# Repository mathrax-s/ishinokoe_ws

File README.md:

# いしのこえWS

いしのこえWSは、MATHRAXの作品「いしのこえ」を紹介・解説しながら、石に触れると音を奏でるちいさな「いしのこえ」をつくるワークショップです。
自分のピンとくる1つの石を選んだら、その相棒となる2つ目の石を選びます。
ここにあるプログラムは、タッチすると音を奏でるプログラムです。

Seeduino XIAOにプログラムします。
<hr />
<p align="center">
</img></img>
<hr />
</img>
<hr />
</p>

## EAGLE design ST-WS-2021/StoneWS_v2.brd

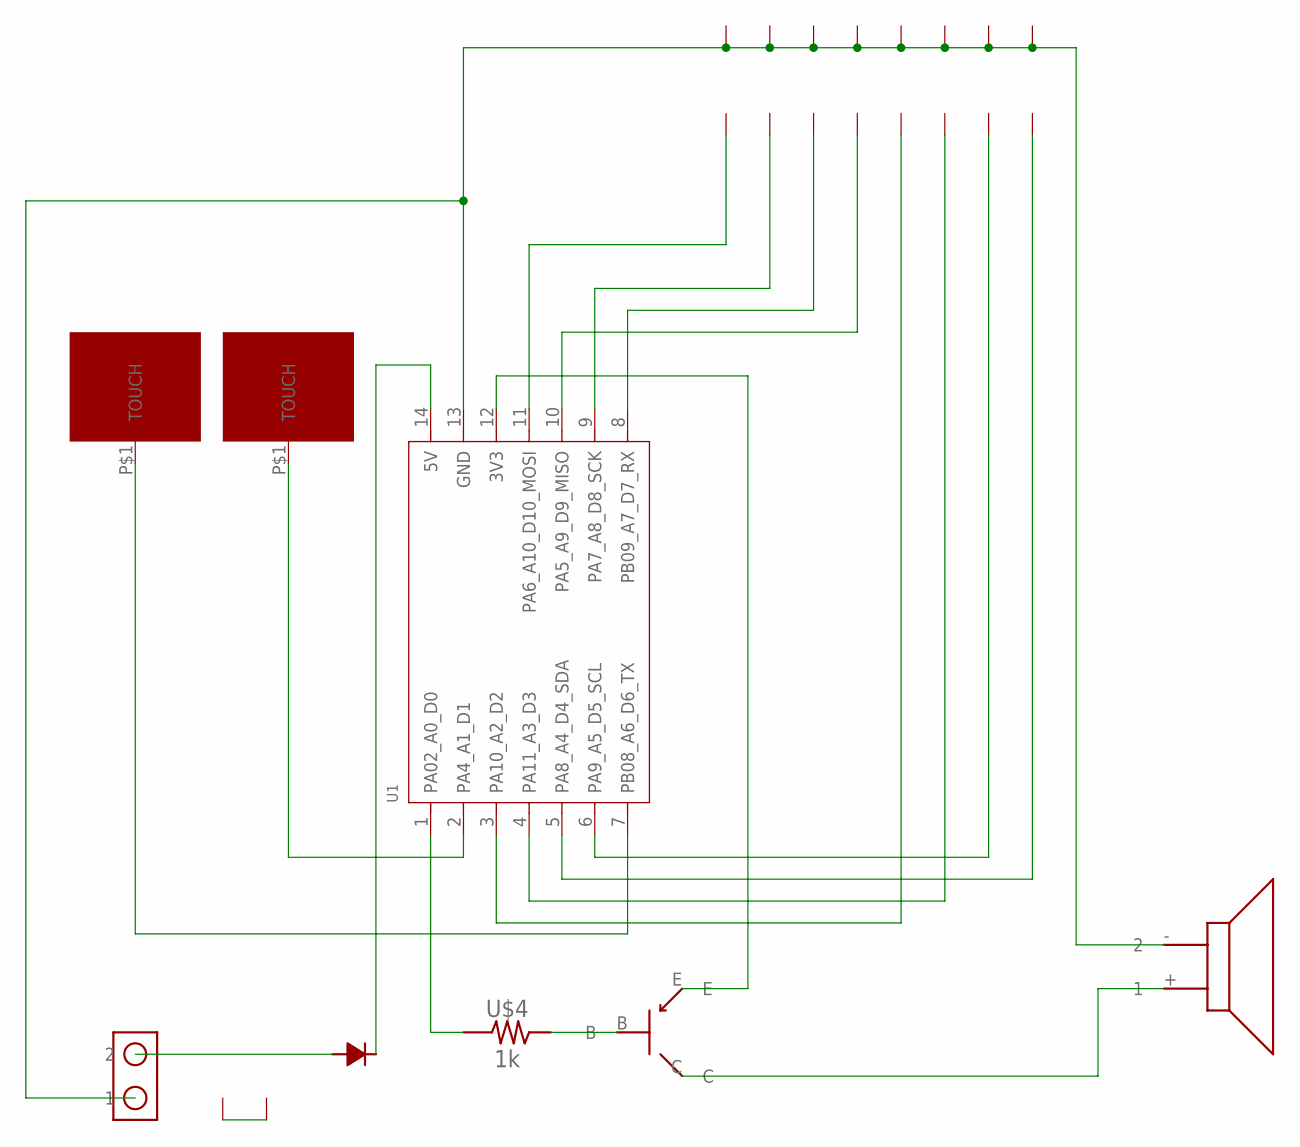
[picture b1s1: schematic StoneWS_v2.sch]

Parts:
U1: MOUDLE-SEEEDUINO-XIAO; MOUDLE14P-2.54-21X17.8MM
U$1: EH2-SMALL-OFFSET; EH2_SMALL-OFFSET
U$2: SPEAKER
U$3: TR-PNP
U$4: 1k; RESC1608X70N
U$6: DIODE-SS2040L
U$7, U$8: TOUCH-PTN-FL1; TOUCH-FLAT1
U$9: M-LOGO
U$10: DIPSWITCH-8

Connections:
unnamed: U1.2 (PA4_A1_D1), U$7.P$1
unnamed: U1.11 (PA6_A10_D10_MOSI), U$10.21
unnamed: U$1.2, U$6.P$1 (1)
unnamed: U$3.B, U$4.2
unnamed: U1.12 (3V3), U$3.E
unnamed: U1.14 (5V), U$6.P$2 (2)
unnamed: U1.7 (PB08_A6_D6_TX), U$8.P$1
unnamed: U1.1 (PA02_A0_D0), U$4.1
unnamed: U1.13 (GND), U$1.1, U$2.- (2), U$10.11, U$10.12, U$10.13, U$10.14, U$10.15, U$10.16, U$10.17, U$10.18
unnamed: U1.9 (PA7_A8_D8_SCK), U$10.22
unnamed: U$9.P$1 (1), U$9.P$2 (2)
unnamed: U1.10 (PA5_A9_D9_MISO), U$10.24
unnamed: U1.3 (PA10_A2_D2), U$10.25
unnamed: U1.4 (PA11_A3_D3), U$10.26
unnamed: U1.5 (PA8_A4_D4_SDA), U$10.28
unnamed: U1.6 (PA9_A5_D5_SCL), U$10.27
unnamed: U$2.+ (1), U$3.C
unnamed: U1.8 (PB09_A7_D7_RX), U$10.23

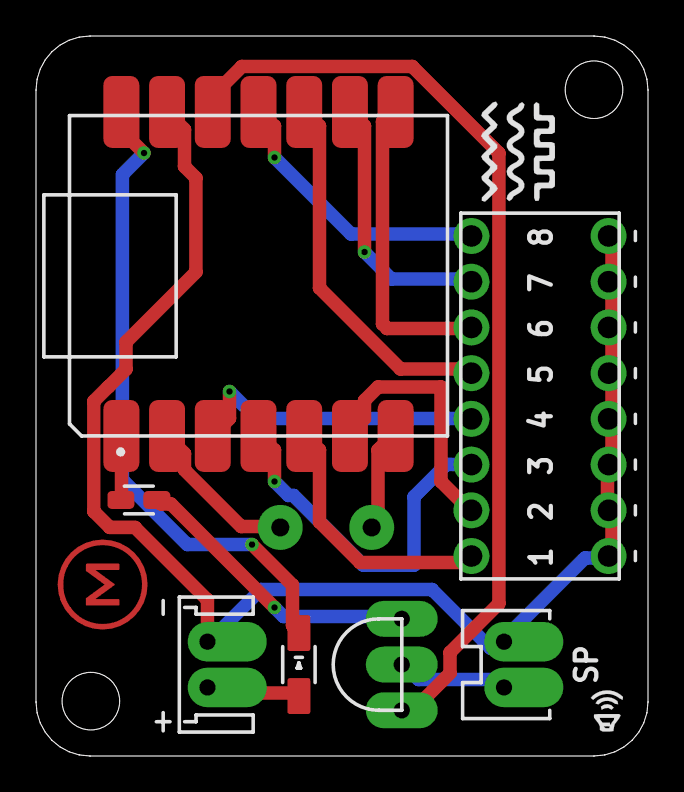
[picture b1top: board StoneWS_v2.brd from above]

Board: 2 copper layers, 34.0 x 40.0 mm, 10 parts (0 on the bottom side), 18 nets.

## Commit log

2022-10-25 いしのこえWS・プラグラム
2022-11-08 2022/11/08
2022-11-08 image upload
